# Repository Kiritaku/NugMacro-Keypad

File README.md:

# NugMacro-Keypad
 This is my first (working)attempt at designing/assembling a keyboard from scratch.
 I'll try to include some issues I had, and how I resolved them for others to look at when troubleshooting their own designs, and for myself.
 
### Preface/Disclaimer
 For anyone reading this trying to troubleshoot their own project. If you have not realized this yet, especially if this is your first attemp at something like this, realize  that troubleshooting will be the most time consuming part of this. After all, it's always a learning experince, and thats just the nature of it.
- **Disclaimer** to anyone reading this. My understanding is that this project uses a bit of outdated components with the mcu, power connector, and daughterboard as theres definetely better MCU options and now better daughterboard options. I originally began this in 2020, so please don't use my schematic or parts list as a bible for building your own.

### Learning How To Use KiCAD
- The popular EDA of choice is [KiCAD](https://www.kicad.org/). It's free and not incredibly hard to learn. 
- YouTube videos worked best for me to get started.
- Going through KiCAD's doc page is incredibly helpful for any issues videos can't help you solve.
- Like with any new software, it's going to take a lot of time to really understand it, but try not to get discouraged.
 
### Schematic Issues
- Try to keep everything organized for yours, and others sake.
- Flags are your friend for organization.
- Try to look at it from the perspective of someone else every now and then. Noone wants to try to understand a shitty schematic, and if you take a long break from working on it, it's a pain in the ass to know what you were doing (Learned this the hard way).
- For footprints and symbols, there are some great libraries from people like [Ai03](https://github.com/ai03-2725) and [EBastler](https://github.com/ebastler). You can learn to make your own, but for your first attempt theres not a whole lot of reason to do that to yourself.
- When actually choosing your components, look at the datasheet for your chosen MCU. It's got everything you need to know for the basic requirements.

### PCB Issues
- If you already know how you want the outline of your PCB to look like, make sure your components will fit into this well to make it easy to route later.
- For USB connections, route your data lines in a close to equal length, with no other traces under or over them.
- Make your traces and layout look good. Your spending a lot of time to create this, and when you finally see the physical result, you want it to look intentional and thoughtful.
- Try to keep your crystal close to your MCU, and keep other traces away from it if they don't need to be there. A ground fill around it is also good for reducing possible interference.
- This took me longer to realize than it should have, but don't try to connect the ground net through a messy spiderweb of traces. Use a ground fill.
- Orient your MCU in whatever way makes it easist, and  prettiest, to route.

### Adding Artwork
- If you want, you can add drawings or other symbols/lettering to your silkscreen using something like [SVG to Shenzen](https://github.com/badgeek/svg2shenzhen).

### Manufacturing
- I ordered my boards from [JLCPCB](https://jlcpcb.com/).
- When making the production files, there are plugins for KiCAD that can make this easier, but just make sure you verify it looks correct.
- When selecting components for assmebly, make sure they are all correct. I had an issue from choosing a crystal at the correct speed, but wrong load.
- I used this formula **_(CL = (C1 * C2) / (C1 + C2) + Cstray)_** for finding what load rating I needed for my crystal. C1 and C2 are the caps for your crystal and I used **5pF** for my stray approximation.
- **For the love of god** do not try to assemble the entire board yourself thinking it wont be that hard.
- After you buy all the parts, ship everything, and assemble it. The time and money spent is not worth getting at least the majority of the board assembled form JLC.
- Especially if you try to do this all with a soldering iron, it can definetly be done, but there is a *__Lot__* of room for mistakes
- I did it thinking it would be good experince, and thinking it would be cool to do it all myself. It wasn't, mistakes are expensive, a lot can and did go wrong for me, and soldering experince will in no way make you immune to these mistakes.
- Given all of that, it is kinda fun doing it all yourself.
- And for components, I just uploaded my BOM to [DigiKey](https://www.digikey.com/) and ordered from them.
### Writing The Code
- I'll add info on this later, sorry.

### Case and Plate
- If you 3D print this yourself, make sure you have a well calibrated printer.
- I opted to use a piece of FR4 that I then lasercut to size.
- You can use a plate generator like this one from [swillkb](http://builder.swillkb.com/) to make it easier.
- I am currently working on a walnut case for my board, but when designing your case. Make sure you account for your desired mounting style, and daughterboard or any additional components you may have.

 ### Notes
 - I'll add some helpful links later.
 - I'll get these files organized a bit better/remove a good bit of junk soon.
 - Prob need to condense/organize this better.
 - If anyone has any questions about your own project or mine. Shoot me an email (Logan@Scootah.dev) and I'll do my best to give you a good answer.

 ### UPDATE
 Project is on hiatus for now, but if for whatever reason someone builds one of their own, qmk firmware is finished and if you want it just email me. 
 P.S. I wired the OLED wrong so prob wanna put it on the correct pins if you make your own to save a headache.

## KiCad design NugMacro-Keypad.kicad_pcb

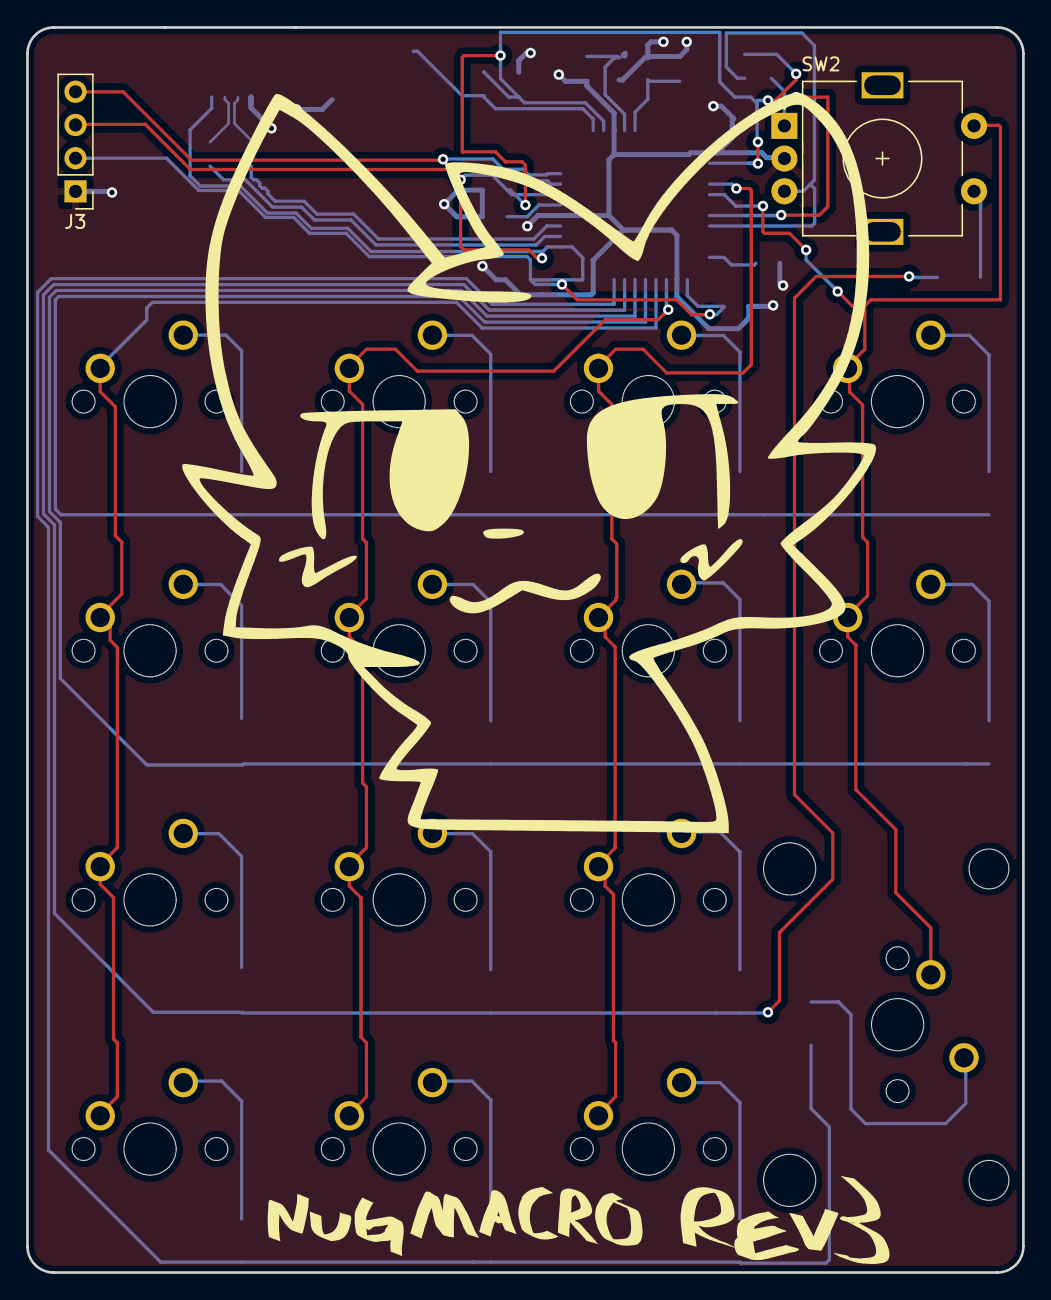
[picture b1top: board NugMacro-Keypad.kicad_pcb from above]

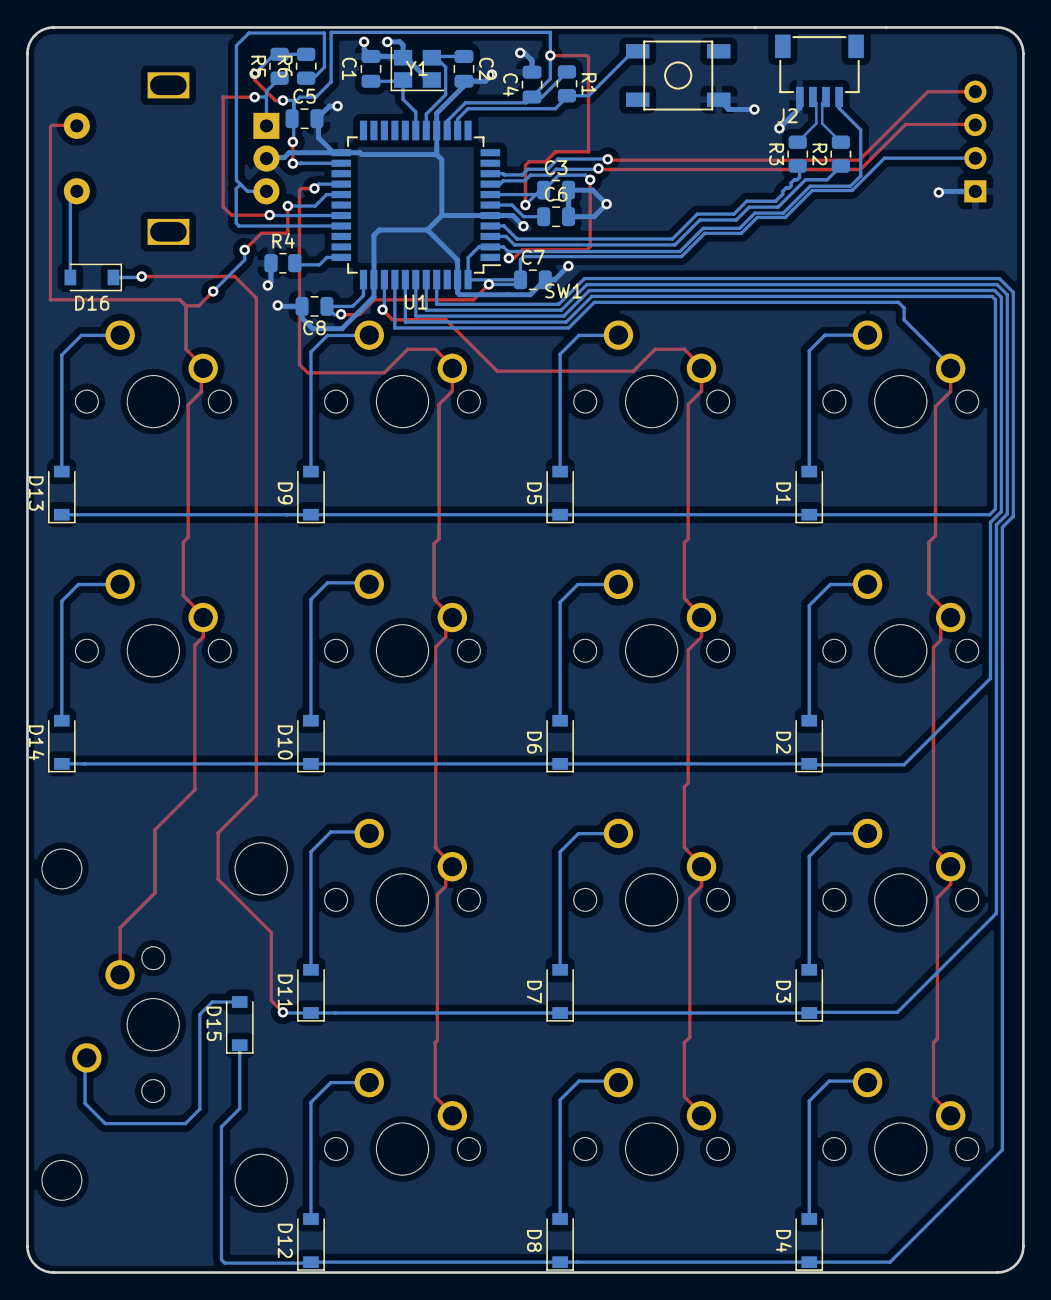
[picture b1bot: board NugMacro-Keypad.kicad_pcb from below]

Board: 2 copper layers, 76.2 x 95.2 mm, 51 parts (34 on the bottom side), 39 nets.

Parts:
C1, C2: 22pF; C_0805_2012Metric
C3, C4, C5, C8: 0.1uF; C_0805_2012Metric
C6: 1uF; C_0805_2012Metric
C7: 10uF; C_0805_2012Metric
D1, D2, D3, D4, D5, D6, D7, D8, D9, D10, D11, D12, D13, D14, D15, D16: D_Small; D_SOD-123
J2: Conn_01x04; JST-SR-4
J3: Conn_01x04_Female_For_LCD; PinHeader_1x04_P2.54mm_Vertical
MX1: #1; MXOnly-1U-NoLED
MX2: #1b; MXOnly-1U-NoLED
MX3: #1c; MXOnly-1U-NoLED
MX4: #1d; MXOnly-1U-NoLED
MX5: #2; MXOnly-1U-NoLED
MX6: #2b; MXOnly-1U-NoLED
MX7: #2c; MXOnly-1U-NoLED
MX8: #2d; MXOnly-1U-NoLED
MX9: #3; MXOnly-1U-NoLED
MX10: #3b; MXOnly-1U-NoLED
MX11: #3c; MXOnly-1U-NoLED
MX12: #3d; MXOnly-1U-NoLED
MX13: #4; MXOnly-1U-NoLED
MX14: #4b; MXOnly-1U-NoLED
MX15: #4c; MXOnly-2U-NoLED
R1, R4: 10k; R_0805_2012Metric
R2, R3: 22; R_0805_2012Metric
R5, R6: 10K; R_0805_2012Metric
SW1: SW_Push; SKQG-1155865
SW2: RotaryEncoder_Switch; RotaryEncoder_Alps_EC11E-Switch_Vertical_H20mm
U1: ATmega32U4-A; TQFP-44_10x10mm_P0.8mm
Y1: 16MHz; Crystal_SMD_3225-4Pin_3.2x2.5mm

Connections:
+5V: C3.1, C4.1, C5.1, C7.1, C8.1, J2.1, J3.2, R1.1, R5.2, R6.2, U1.2 (UVCC), U1.7 (VBUS), U1.14 (VCC), U1.24 (AVCC), U1.34 (VCC), U1.44 (AVCC)
CLK: R5.1, SW2.A, U1.29 (PB5)
COL0: MX1.1 (COL), MX2.1 (COL), MX3.1 (COL), MX4.1 (COL), U1.37 (PF6)
COL1: MX5.1 (COL), MX6.1 (COL), MX7.1 (COL), MX8.1 (COL), U1.36 (PF7)
COL2: MX9.1 (COL), MX10.1 (COL), MX11.1 (COL), MX12.1 (COL), U1.26 (PD6)
COL3: MX13.1 (COL), MX14.1 (COL), MX15.1 (COL), SW2.S2, U1.27 (PD7)
D+: J2.3, R3.2
D-: J2.2, R2.2
DT: R6.1, SW2.B, U1.30 (PB6)
GND: C1.2, C2.2, C3.2, C4.2, C5.2, C6.2, C7.2, C8.2, J2.4, J3.1, R4.1, SW1.1, SW2.C, U1.5 (UGND), U1.15 (GND), U1.23 (GND), U1.35 (GND), U1.43 (GND), Y1.2, Y1.4
unnamed: C6.1, U1.6 (UCAP)
unnamed: D1.2 (A), MX1.2 (ROW)
unnamed: D2.2 (A), MX2.2 (ROW)
unnamed: D3.2 (A), MX3.2 (ROW)
unnamed: D4.2 (A), MX4.2 (ROW)
unnamed: D5.2 (A), MX5.2 (ROW)
unnamed: D6.2 (A), MX6.2 (ROW)
unnamed: D7.2 (A), MX7.2 (ROW)
unnamed: D8.2 (A), MX8.2 (ROW)
unnamed: D9.2 (A), MX9.2 (ROW)
unnamed: D10.2 (A), MX10.2 (ROW)
unnamed: D11.2 (A), MX11.2 (ROW)
unnamed: D12.2 (A), MX12.2 (ROW)
unnamed: D13.2 (A), MX13.2 (ROW)
unnamed: D14.2 (A), MX14.2 (ROW)
unnamed: D15.2 (A), MX15.2 (ROW)
unnamed: D16.2 (A), SW2.S1
unnamed: R2.1, U1.3 (D-)
unnamed: R3.1, U1.4 (D+)
unnamed: R4.2, U1.33 (~HWB/PE2)
OLED1: J3.4, U1.9 (PB1)
OLED2: J3.3, U1.8 (PB0)
RESET: R1.2, SW1.2, U1.13 (~RESET)
ROW0: D1.1 (K), D5.1 (K), D9.1 (K), D13.1 (K), U1.38 (PF5)
ROW1: D2.1 (K), D6.1 (K), D10.1 (K), D14.1 (K), U1.39 (PF4)
ROW2: D3.1 (K), D7.1 (K), D11.1 (K), D16.1 (K), U1.40 (PF1)
ROW3: D4.1 (K), D8.1 (K), D12.1 (K), D15.1 (K), U1.41 (PF0)
XTAL1: C1.1, U1.17 (XTAL1), Y1.1
XTAL2: C2.1, U1.16 (XTAL2), Y1.3

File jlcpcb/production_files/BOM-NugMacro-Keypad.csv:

Comment,Designator,Footprint,LCSC
#4b,MX14,MX-1U-NoLED,
#1,MX1,MX-1U-NoLED,
#2c,MX7,MX-1U-NoLED,
#4,MX13,MX-1U-NoLED,
#2d,MX8,MX-1U-NoLED,
#3b,MX10,MX-1U-NoLED,
#1b,MX2,MX-1U-NoLED,
#3d,MX12,MX-1U-NoLED,
#3c,MX11,MX-1U-NoLED,
RotaryEncoder_Switch,SW2,RotaryEncoder_Alps_EC11E-Switch_Vertical_H20mm,
#4c,MX15,MX-2U-NoLED,
#1c,MX3,MX-1U-NoLED,
#1d,MX4,MX-1U-NoLED,
Conn_01x04_Female_For_LCD,J3,PinHeader_1x04_P2.54mm_Vertical,
#2b,MX6,MX-1U-NoLED,
#2,MX5,MX-1U-NoLED,
#3,MX9,MX-1U-NoLED,
22,R3,R_0805_2012Metric,
D_Small,D3,D_SOD-123,
D_Small,D4,D_SOD-123,
0.1uF,C4,C_0805_2012Metric,
D_Small,D8,D_SOD-123,
ATmega32U4-A,U1,TQFP-44_10x10mm_P0.8mm,
10k,R4,R_0805_2012Metric,
22,R2,R_0805_2012Metric,
D_Small,D15,D_SOD-123,
D_Small,D16,D_SOD-123,
Conn_01x04,J2,JST-SR-4,
0.1uF,C3,C_0805_2012Metric,
10K,R6,R_0805_2012Metric,
D_Small,D14,D_SOD-123,
D_Small,D10,D_SOD-123,
10k,R1,R_0805_2012Metric,
SW_Push,SW1,SKQG-1155865,
D_Small,D6,D_SOD-123,
22pF,C1,C_0805_2012Metric,
D_Small,D12,D_SOD-123,
16MHz,Y1,Crystal_SMD_3225-4Pin_3.2x2.5mm,
22pF,C2,C_0805_2012Metric,
D_Small,D9,D_SOD-123,
D_Small,D11,D_SOD-123,
D_Small,D5,D_SOD-123,
D_Small,D1,D_SOD-123,
1uF,C6,C_0805_2012Metric,
0.1uF,C8,C_0805_2012Metric,
D_Small,D2,D_SOD-123,
D_Small,D7,D_SOD-123,
10uF,C7,C_0805_2012Metric,
10K,R5,R_0805_2012Metric,
0.1uF,C5,C_0805_2012Metric,
D_Small,D13,D_SOD-123,

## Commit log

2022-12-31 Initialize Project
2022-12-31 Add submodules
2022-12-31 Add Libraries
2022-12-31 Wiring MCU
2023-01-01 Board layout dxf's and usb-c footprints
2023-01-01 Reset circuit in schema
2023-01-07 auto save
2023-05-24 fixed fucky wucky on mcu
2023-05-25 added encoder and oled with matrix
2023-05-25 schema finished with footprints assigned
2023-05-26 fixed annotations and oled footprint
2023-05-26 components placed on pcb and cut line should be fixed, routing will be next
2023-05-26 Rev3 board outline, usb placement in middle makes for tough routing so moved to left
2023-05-27 lil schema and pcb changes
    flipped/ changed around smd components so it may be easier to route, got rid of reset pins for simplicity sake with small board
2023-06-25 cant remember lol
    may need to go to commit before this one well see
2023-08-05 routing changes
    routed keyswitch matrix. Have not done supporting components yet.
2023-08-05 routing changes again
    finished some routing going to change column/row flags hopefully works heres this if it dont.
2023-08-05 First prototype pcb done
    finally
2023-08-05 making gerber files
    idk
2023-08-06 finished pcb aside from silkscreen
    next update will be of silkscreen design but as of now pcb is ready for plotting.
2023-08-06 silkscreen art
    silkscreen stuf done
2023-08-06 production files done
    yayyyyyy
2023-08-07 ssilkcreen changess
    added cat
2023-08-07 done for now time to order
    updated pcb grounds and silkscreen
2023-08-07 its done
    yay
2023-08-12 starting rev 3 improvements
    now that i have a working prototype making small changes, changed switches to mx only, and cleaned up some routing so far.
2023-08-12 fixed zones and some routing
    might be done here for this project idk for sure yet. cant decide if i want to add anything else, but looks much better now.
2023-09-04 idk
    its somethin
2023-09-04 y
    y
2023-09-04 Second Version of Rev3 ig?
    fixed wiring on oled, made 1.5u key look a bit better, pulled back the jst connector to hopefully make compatible for a rubber o ring gasket mount.
2023-09-04 better? revision ordered
    idk
2023-09-06 just double checked some possible design rule issues
2023-10-05 Plate changes
    just gonna do plate in fusion now
2023-10-05 fusion plate test print
    idk
2023-10-06 Create Case print test_.stl
    testing out a lil case design
2023-10-12 stuf
    idkl
2023-10-12 Create Plate wiht top fifth test 1 v1.stl
    testing plates
2023-11-03 Organized

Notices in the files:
NugMacro-Keypad.kicad_pcb:
MIT License
